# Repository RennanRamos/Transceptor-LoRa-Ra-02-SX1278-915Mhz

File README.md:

# Transceptor-LoRa-Ra-02-SX1278-915Mhz

## Repositório da disciplina Sistemas Embarcados

Alunos:
  - Rennan de Aguiar Ramos
  - Allan Bispo Nascimento
  - Witória Manuely

Curso: Engenharia de Computação.

## Aplicação 
Desenvolvimento de firmware do tipo driver para controle de transceptor LoRa - SX1278 915Mhz utilizando interface SPI em conjunto com microcontrolador RP2040. O firmware poderá ser aplicado no contexto de monitoramento de recursos a escolha do usuário da aplicação

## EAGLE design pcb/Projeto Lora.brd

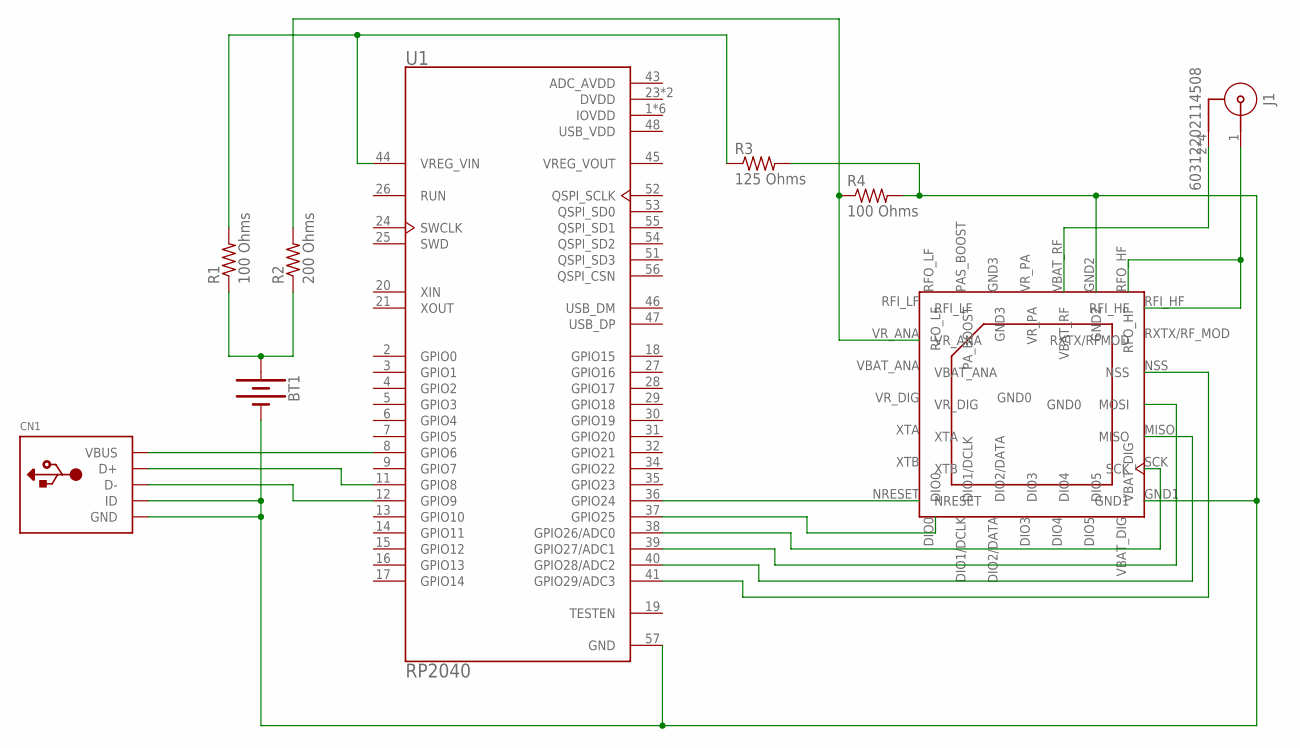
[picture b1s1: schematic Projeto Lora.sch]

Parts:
BT1: BATTERY-9V; BATTCON_9V
CN1: USBMINIB; USB-MINIB
J1: 60312202114508
R1, R4: 100 Ohms; R01005
R2: 200 Ohms; R01005
R3: 125 Ohms; R01005
U1: RP2040; QFN40P700X700X90-57N
U$1: LORA-SX1278; PDIP

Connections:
ADC_AVDD: U1.43 (ADC_AVDD)
DVDD: U1.23 (DVDD), U1.50 (DVDD)
GND0: U$1.GND0
GND3: U$1.GND3
IOVDD: U1.1 (IOVDD), U1.10 (IOVDD), U1.22 (IOVDD), U1.33 (IOVDD), U1.42 (IOVDD), U1.49 (IOVDD)
unnamed: U1.38 (GPIO26/ADC0), U$1.SCK
unnamed: U1.39 (GPIO27/ADC1), U$1.MOSI
unnamed: U1.40 (GPIO28/ADC2), U$1.MISO
unnamed: U1.41 (GPIO29/ADC3), U$1.NSS
unnamed: U1.36 (GPIO24), U$1.NRESET
unnamed: U1.37 (GPIO25), U$1.DIO0
unnamed: J1.1, U$1.RFI_HF, U$1.RFO_HF
unnamed: R2.2, R4.1, U$1.VR_ANA
unnamed: J1.2, J1.3 (2), J1.4 (2), J1.5 (2), U$1.VBAT_RF
unnamed: CN1.D+, U1.11 (GPIO8)
unnamed: BT1.+, R1.1, R2.1
unnamed: CN1.VBUS, U1.8 (GPIO6)
unnamed: R1.2, R3.1, U1.44 (VREG_VIN)
unnamed: CN1.D-, U1.12 (GPIO9)
unnamed: BT1.-, CN1.GND, CN1.ID, R3.2, R4.2, U1.57 (GND), U$1.GND1, U$1.GND2
USB_VDD: U1.48 (USB_VDD)
VBAT_ANA: U$1.VBAT_ANA
VBAT_DIG: U$1.VBAT_DIG
VR_DIG: U$1.VR_DIG
VR_PA: U$1.VR_PA

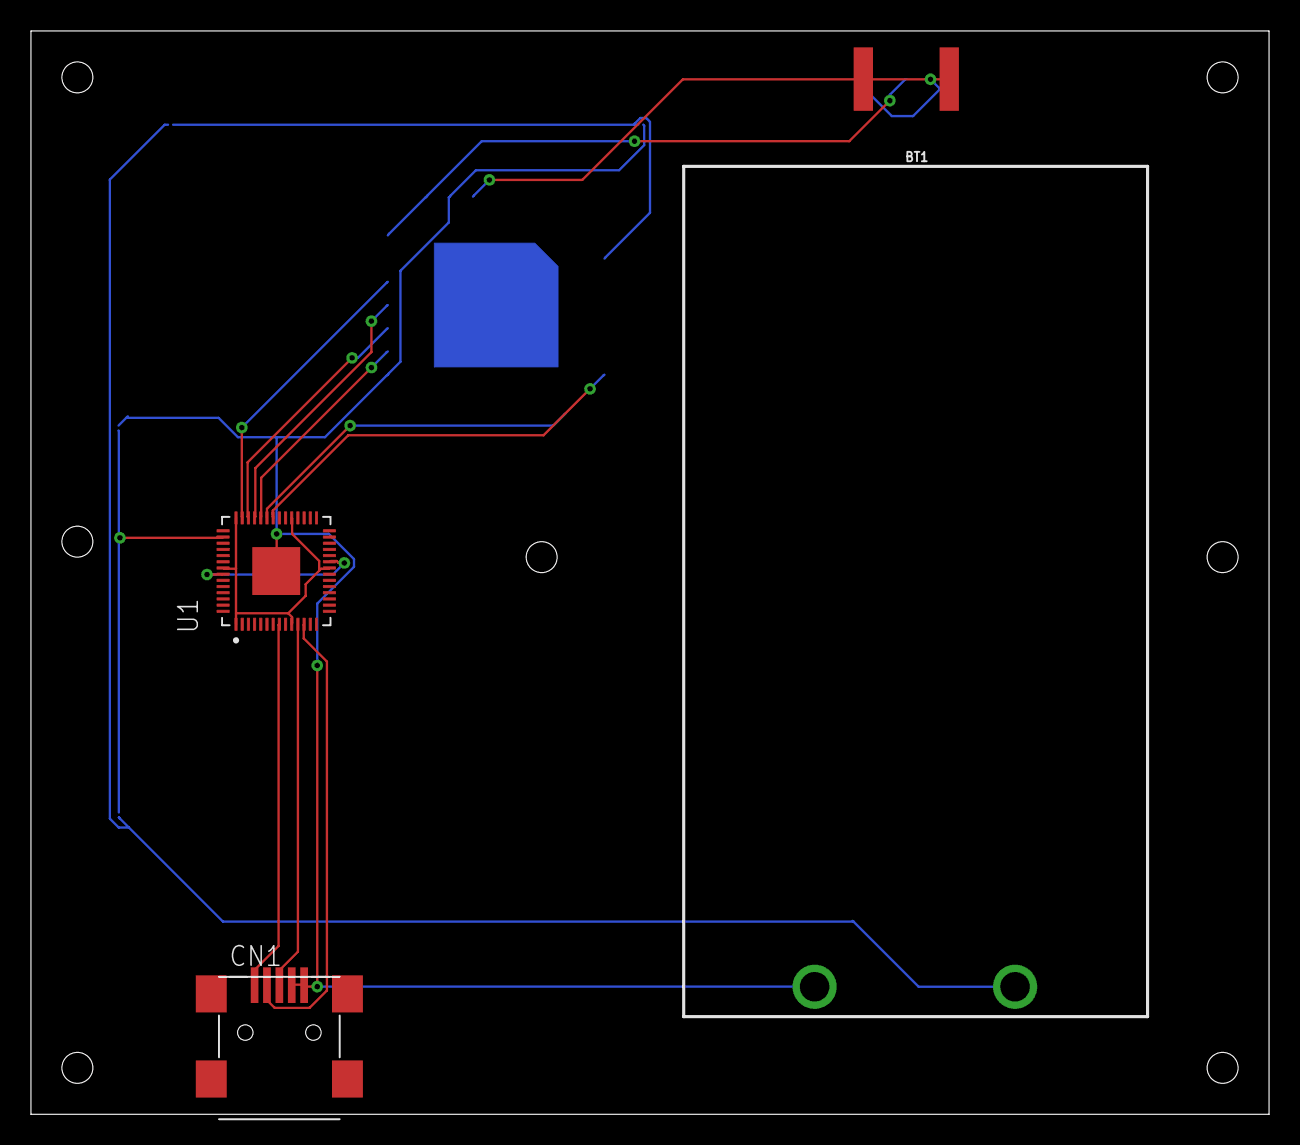
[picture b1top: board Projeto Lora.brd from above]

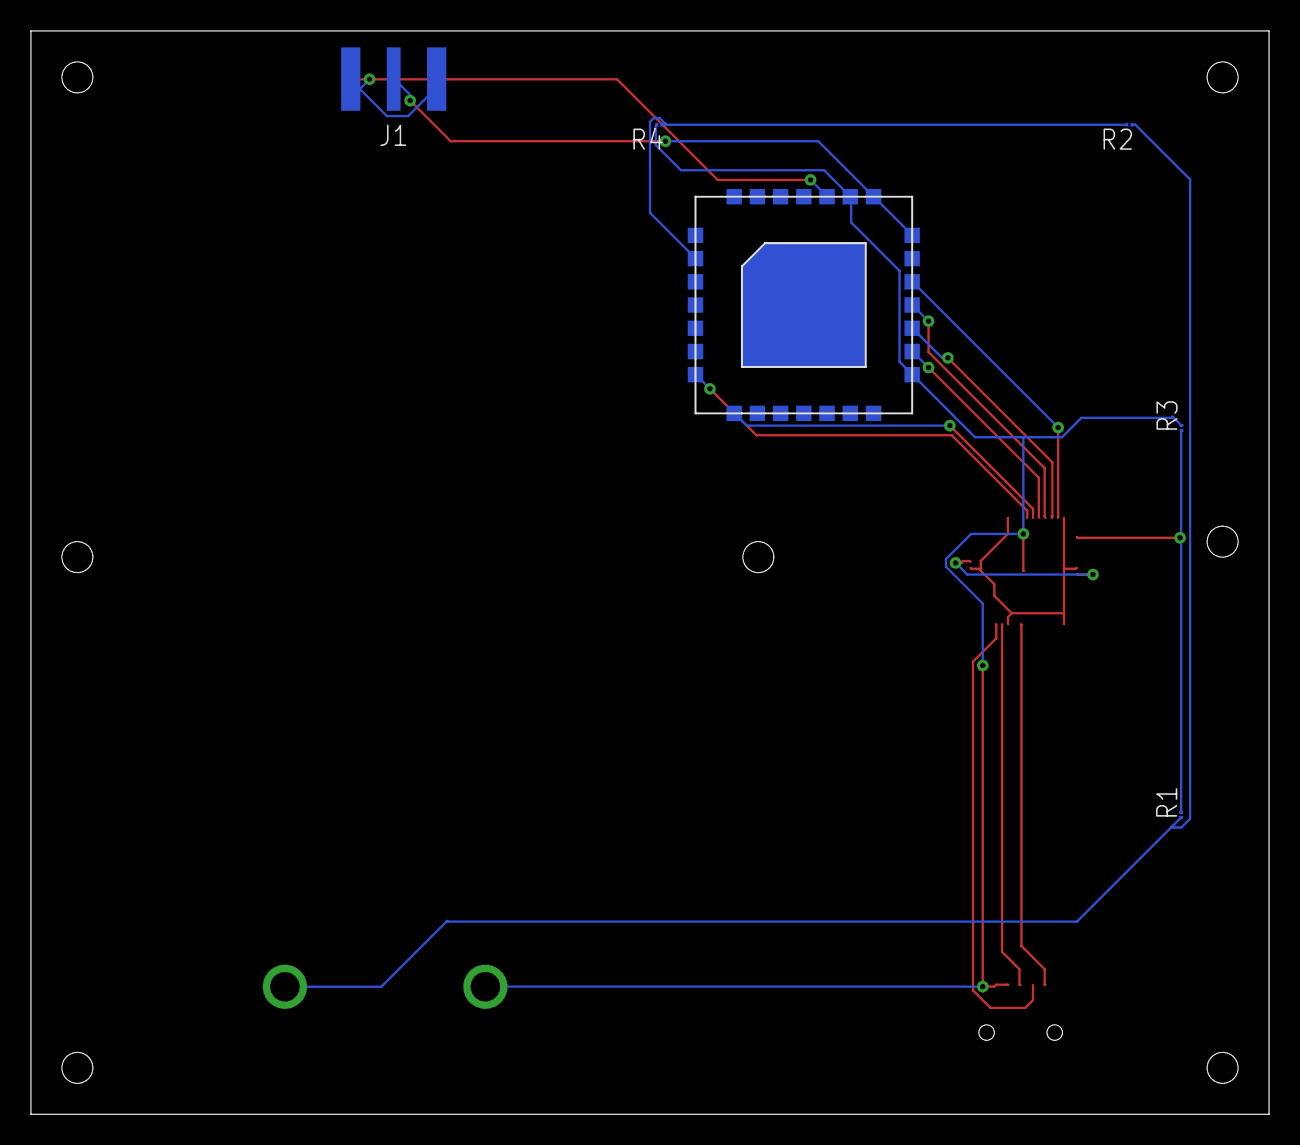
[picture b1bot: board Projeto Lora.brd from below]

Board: 2 copper layers, 80.0 x 70.0 mm, 9 parts (6 on the bottom side), 17 nets.

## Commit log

2021-08-07 Adicionando diretorios
2021-08-08 Adicao de datasheets - Transceptor & RP2040
2021-09-27 Adicionando pasta de importar os videos
2021-09-28 Adicionando documentação escrita que esquecemos de adicionar junto com as demais coisas ontem
2021-10-15 Adicionando pcb e case
2021-10-15 Removendo arquivos antigos
2021-10-16 organizando firmware
2021-10-16 Adicionando video
2021-10-16 utilizacao de bibliotecas Raspberry Pi Pico

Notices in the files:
parts and their libraries:
SparkFun-Batteries: Licensing: Creative Commons ShareAlike 4.0 International - https://creativecommons.org/licenses/by-sa/4.0
